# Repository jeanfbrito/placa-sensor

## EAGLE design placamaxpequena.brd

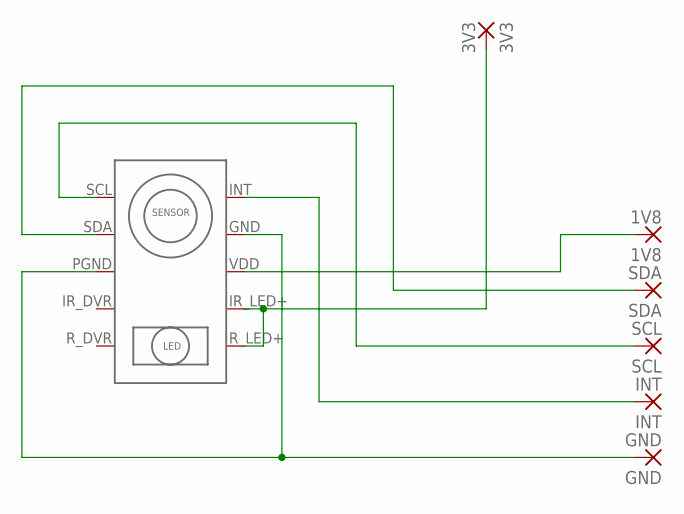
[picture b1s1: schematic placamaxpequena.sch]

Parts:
1V8: 1V8; SMD1,27-2,54
3V3: 3V3; SMD1,27-2,54
GND: GND; SMD1,27-2,54
INT: INT; SMD1,27-2,54
SCL: SCL; SMD1,27-2,54
SDA: SDA; SMD1,27-2,54
U$1: MAX30100; SOIC14

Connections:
1V8: 1V8.1, U$1.VDD
3V3: 3V3.1, U$1.IR_LED+, U$1.R_LED+
GND: GND.1, U$1.GND, U$1.PGND
INT: INT.1, U$1.INT
SCL: SCL.1, U$1.SCL
SDA: SDA.1, U$1.SDA

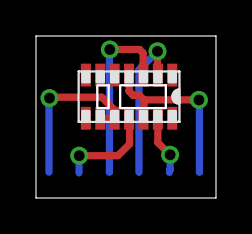
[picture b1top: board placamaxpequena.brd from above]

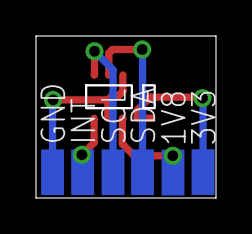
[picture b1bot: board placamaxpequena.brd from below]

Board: 2 copper layers, 9.9 x 8.9 mm, 7 parts (6 on the bottom side), 6 nets.

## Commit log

2016-10-11 :space_invader: Added .gitattributes & .gitignore files
2016-10-12 reduced the board
